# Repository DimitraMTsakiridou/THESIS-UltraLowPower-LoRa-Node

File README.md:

# Custom Ultra-Low Power LoRa Node for Autonomous Telemetry

Aiming to address the challenges of remote water quality monitoring and bypass the complexity of standard LoRaWAN networks, this repository contains the from-scratch design, end-to-end implementation, and extensive experimental evaluation of a custom, energy-autonomous LoRa telemetry node.

<p align="center">
  
  &nbsp; &nbsp;
  
</p>

## 🚀 Key Achievements & Architecture

### 🛠️ Hardware Design
* **Custom PCB:** Designed a 4-layer Printed Circuit Board (PCB) based on the **STM32WL55 System-on-Chip**.
* **Zero Leakage:** Incorporated a PMOS load switch to completely cut off power to the water quality sensors (Atlas Scientific) during sleep periods, eliminating leakage currents.

### 💻 Firmware & Security
* **Protocol:** Developed a lightweight, custom Peer-to-Peer (P2P) communication protocol.
* **Cybersecurity:** Shifted data security to the application layer, utilizing hardware-based **AES-256 encryption** and dynamic frame counters to prevent deliberate replay attacks.

### ⚡ Performance & Energy Efficiency
* **Energy-Neutral Operation:** The custom board records an average consumption of merely **261 μA** per 15-minute duty cycle. This ensures a theoretical battery autonomy of over 400 days. Coupled with a 5W solar panel, the system becomes completely energy-neutral.
* **Long-Range Telemetry:** Established a reliable wireless link over a distance of **11 km** under Line-of-Sight (LoS) conditions, demonstrating outstanding noise immunity (SNR -18 dB).

### 🧪 SDR Validation & Stress Testing
The reliability of the physical layer and the system's cybersecurity were validated in a laboratory environment using Software-Defined Radio (**USRP B210**) equipment. 
* Achieved a **90.4% Packet Delivery Ratio (PDR)** under severe congestion stress tests.
* Successfully prevented deliberate replay and interception attacks.

---
**Keywords:** Water Quality Telemetry, Internet of Things (IoT), LoRa, LPWAN, Custom Hardware (PCB), Energy Harvesting, Cybersecurity, Software-Defined Radio (SDR).

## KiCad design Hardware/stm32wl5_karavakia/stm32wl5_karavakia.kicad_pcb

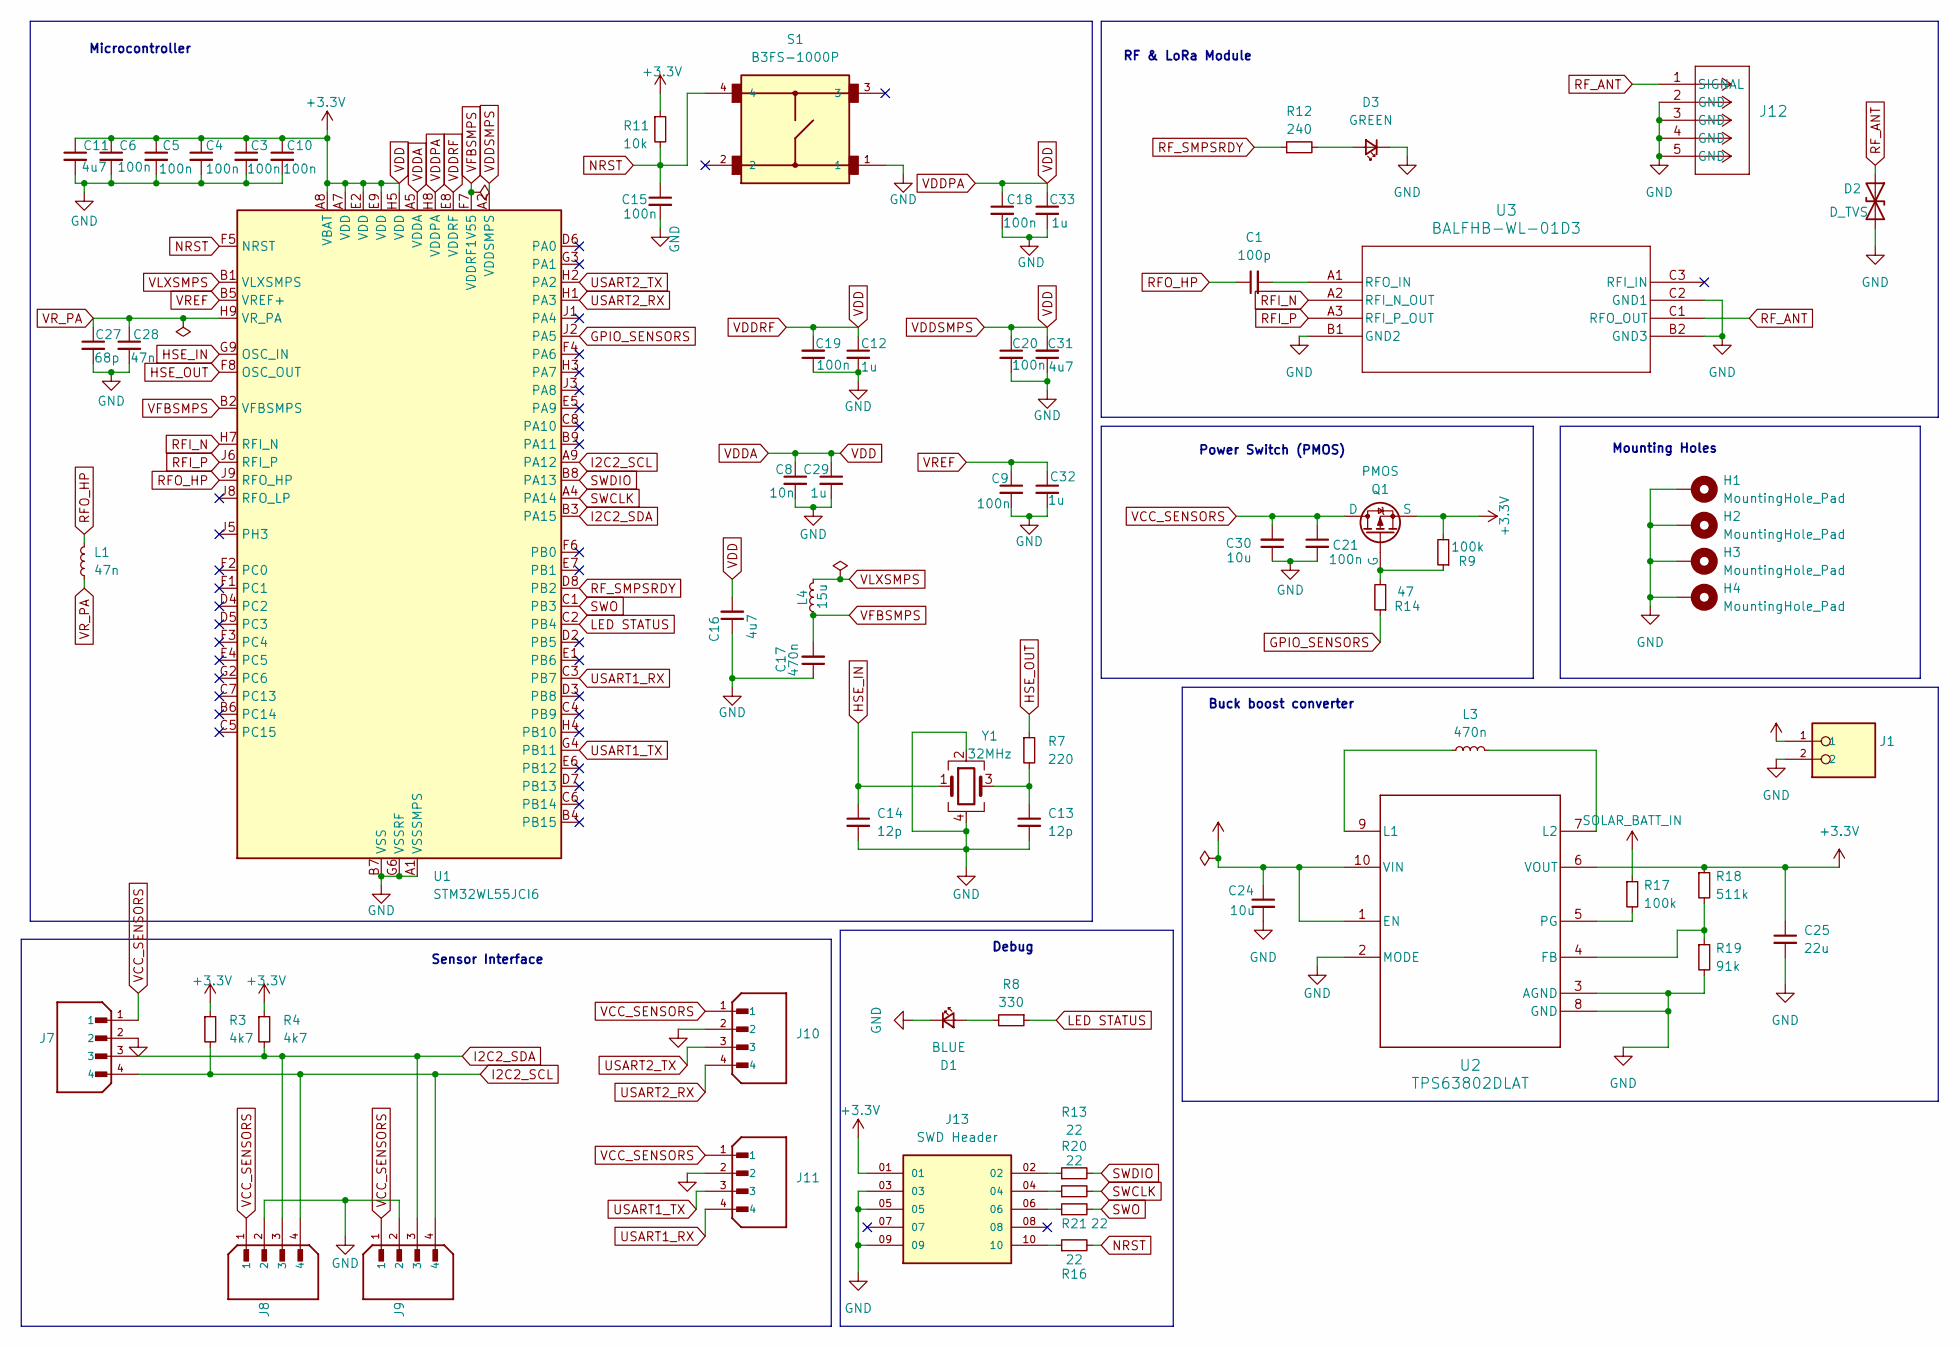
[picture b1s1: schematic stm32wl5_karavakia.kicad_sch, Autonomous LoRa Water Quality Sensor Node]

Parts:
C1: 100p; C_0402_1005Metric
C3, C4, C5, C6, C9, C10, C15, C18, C19, C20, C21: 100n; CAPC1608X90N
C8: 10n; CAPC1608X90N
C11, C16, C31: 4u7; CAPC2012X135N
C12, C29, C32, C33: 1u; CAPC1005X55N
C13, C14: 12p; CAPC1608X90N
C17: 470n; CAPC1608X90N
C24, C30: 10u; CAPC2012X135N
C25: 22u; CAPC2012X140N
C27: 68p; CAPC1005X55N
C28: 47n; CAPC1005X55N
D1: BLUE; LED_XL-2012SURC_XLG
D2: D_TVS; INDC1005X45
D3: GREEN; LED_APT2012_SMD-2P0X1P25_KNB
H1, H2, H3, H4: MountingHole_Pad; MountingHole_3.2mm_M3_Pad_Via
J1: PHOENIX_1935161; PARTREV 14.12.2022
J7, J8, J9, J10, J11: JST_B4B-XH-A; PARTREV 7/4/21
J12: CONN_901-143-6RFX_AMP
J13: SWD Header; SAMTEC_FTSH-105-XX-X-DV; PARTREV H
L1: 47n; LQW15CNR20J00B
L3: 470n; IND_IHLP_1616_BZ_VIS
L4: 15u; INDC2012X145N
Q1: PMOS; SOT-23-3L_AOS
R3, R4: 4k7; R_0805_2012Metric_Pad1.20x1.40mm_HandSolder
R7: 220; R_0805_2012Metric_Pad1.20x1.40mm_HandSolder
R8: 330; R_0805_2012Metric_Pad1.20x1.40mm_HandSolder
R9, R17: 100k; R_0805_2012Metric_Pad1.20x1.40mm_HandSolder
R11: 10k; R_0805_2012Metric_Pad1.20x1.40mm_HandSolder
R12: 240; R_0805_2012Metric_Pad1.20x1.40mm_HandSolder
R13, R16, R20, R21: 22; R_0805_2012Metric_Pad1.20x1.40mm_HandSolder
R14: 47; RES_R0805_ROM
R18: 511k; R_0805_2012Metric_Pad1.20x1.40mm_HandSolder
R19: 91k; R_0805_2012Metric_Pad1.20x1.40mm_HandSolder
S1: B3FS-1000P; SOIC_FS-1000P_OMR
U1: STM32WL55JCI6; UFBGA73_5X5_STM_1
U2: TPS63802DLAT; DLA0010A
U3: BALFHB-WL-01D3; CSPG8_STM
Y1: 32MHz; NX2016SA_NDK

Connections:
GND: C3.2, C4.2, C5.2, C6.2, C8.2, C9.2, C10.2, C11.2, C12.2, C13.2, C14.2, C15.2, C16.1, C17.1, C18.2, C19.1, C20.2, C21.2, C24.2, C25.2, C27.2, C28.2, C29.2, C30.1, C31.1, C32.2, C33.2, D1.1 (K), D2.2 (A2), D3.1 (K), H1.1, H2.1, H3.1, H4.1, J1.2, J7.2, J8.2, J9.2, J10.2, J11.2, J12.2 (GND), J12.3 (GND), J12.4 (GND), J12.5 (GND), J13.03, J13.05, J13.09, R19.2, S1.1, U1.A1 (VSSSMPS), U1.B7 (VSS), U1.D9 (VSS), U1.E3 (VSS), U1.G5 (VSS), U1.G6 (VSSRF), U1.G7 (VSSRF), U1.G8 (VSSRF), U1.H6 (VSSRF), U2.2 (MODE), U2.3 (AGND), U2.8 (GND), U3.B1 (GND2), U3.B2 (GND3), U3.C2 (GND1), Y1.2, Y1.4
GPIO_SENSORS: R14.1, U1.J2 (PA5)
HSE_IN: C14.1, U1.G9 (OSC_IN), Y1.1
HSE_OUT: R7.1, U1.F8 (OSC_OUT)
I2C2_SCL: J7.4, J8.4, J9.4, R3.2, U1.A9 (PA12)
I2C2_SDA: J7.3, J8.3, J9.3, R4.2, U1.B3 (PA15)
LED STATUS: R8.1, U1.C2 (PB4)
NRST: C15.1, R11.2, R16.2, S1.4, U1.F5 (NRST)
unnamed: C13.1, R7.2, Y1.3
unnamed: D1.2 (A), R8.2
unnamed: D3.2 (A), R12.2
unnamed: J13.02, R13.1
unnamed: J13.04, R20.1
unnamed: J13.06, R21.1
unnamed: J13.10, R16.1
unnamed: Q1.2 (G), R9.1, R14.2
unnamed: R18.2, R19.1, U2.4 (FB)
unnamed: L3.1, U2.9 (L1)
unnamed: L3.2, U2.7 (L2)
unnamed: R17.2, U2.5 (PG)
unnamed: C1.2, U3.A1 (RFO_IN)
RFI_N: U1.H7 (RFI_N), U3.A2 (RFI_N_OUT)
RFI_P: U1.J6 (RFI_P), U3.A3 (RFI_P_OUT)
RFO_HP: C1.1, L1.2, U1.J9 (RFO_HP)
RF_ANT: D2.1 (A1), J12.1 (SIGNAL), U3.C1 (RFO_OUT)
RF_SMPSRDY: R12.1, U1.D8 (PB2)
SOLAR_BATT_IN: C24.1, J1.1, R17.1, U2.1 (EN), U2.10 (VIN)
SWCLK: R20.2, U1.A4 (PA14)
SWDIO: R13.2, U1.B8 (PA13)
SWΟ: R21.2, U1.C1 (PB3)
USART1_RX: J11.4, U1.C3 (PB7)
USART1_TX: J11.3, U1.G4 (PB11)
USART2_RX: J10.4, U1.H1 (PA3)
USART2_TX: J10.3, U1.H2 (PA2)
VCC_SENSORS: C21.1, C30.2, J7.1, J8.1, J9.1, J10.1, J11.1, Q1.1 (D)
VDD: C3.1, C4.1, C5.1, C6.1, C8.1, C10.1, C11.1, C12.1, C16.2, C18.1, C19.2, C20.1, C25.1, C29.1, C31.2, C33.1, J13.01, Q1.3 (S), R3.1, R4.1, R9.2, R11.1, R18.1, U1.A2 (VDDSMPS), U1.A5 (VDDA), U1.A7 (VDD), U1.A8 (VBAT), U1.E2 (VDD), U1.E8 (VDDRF), U1.E9 (VDD), U1.H5 (VDD), U1.H8 (VDDPA), U2.6 (VOUT)
VFBSMPS: C17.2, L4.1, U1.B2 (VFBSMPS), U1.F7 (VDDRF1V55)
VLXSMPS: L4.2, U1.B1 (VLXSMPS)
VREF: C9.1, C32.1, U1.B5 (VREF+)
VR_PA: C27.1, C28.1, L1.1, U1.H9 (VR_PA)

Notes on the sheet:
Microcontroller
RF & LoRa Module
Mounting Holes
Debug
Power Switch (PMOS)
Buck boost converter
Sensor Interface

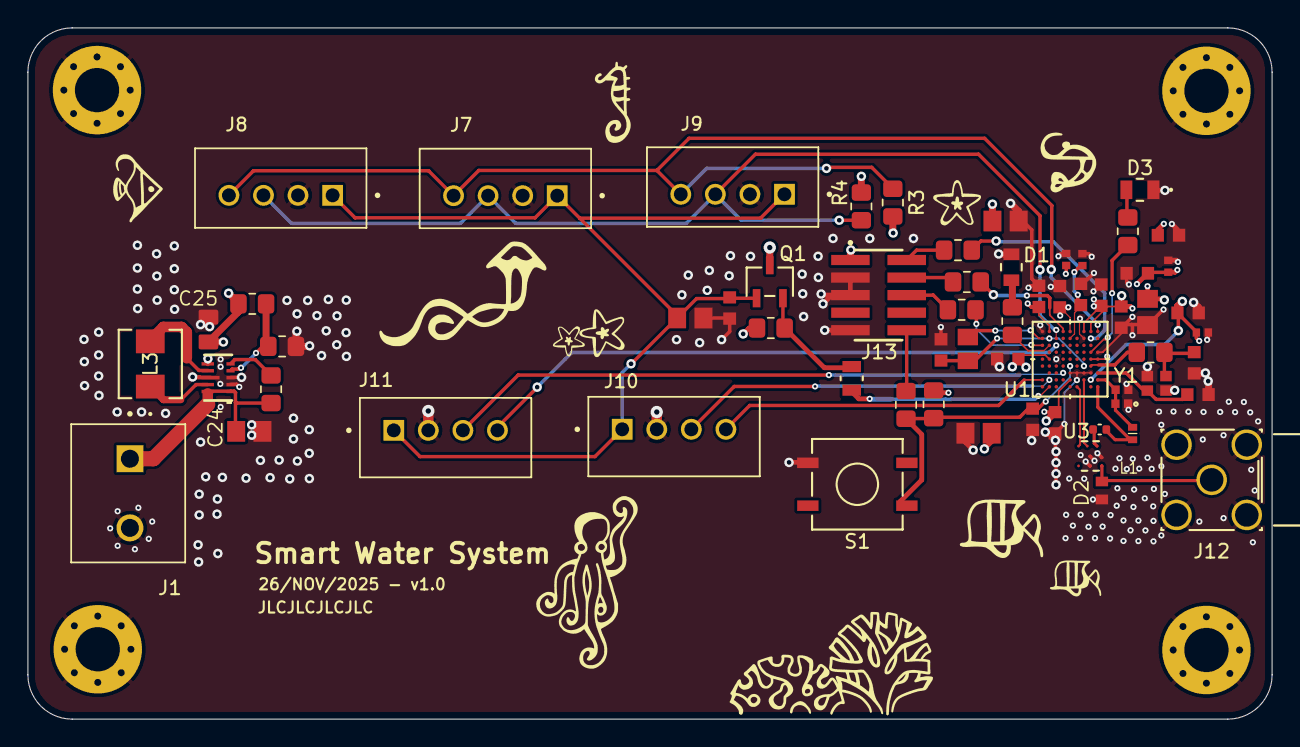
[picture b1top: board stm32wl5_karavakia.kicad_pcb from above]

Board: 4 copper layers, 90.0 x 50.0 mm, 67 parts (0 on the bottom side), 40 nets.

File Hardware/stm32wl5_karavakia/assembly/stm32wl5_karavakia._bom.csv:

"Id";"Designator";"Footprint";"Quantity";"Designation";"Supplier and ref";
1;"C18,C4,C15,C20,C6,C3,C19,C9,C10,C5,C21";"CAPC1608X90N";11;"100n";;;
2;"S1";"SOIC_FS-1000P_OMR";1;"B3F-1000";;;
3;"J12";"COAX4_901-144-8RFX_AMP";1;"~";;;
4;"R21,R20,R13,R16";"R_0805_2012Metric_Pad1.20x1.40mm_HandSolder";4;"22";;;
5;"D3";"LED_APT2012_SMD-2P0X1P25_KNB";1;"GREEN";;;
6;"J8,J7,J10,J9,J11";"JST_B4B-XH-A";5;"~";;;
7;"C8";"CAPC1608X90N";1;"10n";;;
8;"R3,R4";"R_0805_2012Metric_Pad1.20x1.40mm_HandSolder";2;"4k7";;;
9;"U2";"DLA0010A";1;"TPS63802DLAT";;;
10;"D1";"LED_XL-2012SURC_XLG";1;"BLUE";;;
11;"R18";"R_0805_2012Metric_Pad1.20x1.40mm_HandSolder";1;"511k";;;
12;"C11,C31,C16";"CAPC2012X135N";3;"4u7";;;
13;"R12";"R_0805_2012Metric_Pad1.20x1.40mm_HandSolder";1;"240";;;
14;"J13";"SAMTEC_FTSH-105-XX-X-DV";1;"SWD Header";;;
15;"C30,C24";"CAPC2012X135N";2;"10u";;;
16;"R7";"R_0805_2012Metric_Pad1.20x1.40mm_HandSolder";1;"220";;;
17;"U3";"CSPG8_STM";1;"BALFHB-WL-01D3";;;
18;"Q1";"SOT-23-3L_AOS";1;"PMOS";;;
19;"R14";"RES_R0805_ROM";1;"47";;;
20;"C25";"CAPC2012X140N";1;"22u";;;
21;"C17";"CAPC1608X90N";1;"470n";;;
22;"C12,C32,C33,C29";"CAPC1005X55N";4;"1u";;;
23;"C1";"C_0402_1005Metric";1;"100p";;;
24;"C28";"CAPC1005X55N";1;"47n";;;
25;"C27";"CAPC1005X55N";1;"68p";;;
26;"R9,R17";"R_0805_2012Metric_Pad1.20x1.40mm_HandSolder";2;"100k";;;
27;"Y1";"NX2016SA_NDK";1;"32MHz";;;
28;"L1";"LQW15CNR20J00B";1;"47n";;;
29;"J1";"PHOENIX_1935161";1;"~";;;
30;"R8";"R_0805_2012Metric_Pad1.20x1.40mm_HandSolder";1;"330";;;
31;"R11";"R_0805_2012Metric_Pad1.20x1.40mm_HandSolder";1;"10k";;;
32;"L3";"IND_IHLP_1616_BZ_VIS";1;"470n";;;
33;"L4";"INDC2012X145N";1;"15u";;;
34;"C14,C13";"CAPC1608X90N";2;"12p";;;
35;"R19";"R_0805_2012Metric_Pad1.20x1.40mm_HandSolder";1;"91k";;;
36;"D2";"INDC1005X45";1;"D_TVS";;;
37;"U1";"UFBGA73_5X5_STM_1";1;"STM32WL55JCI6";;;

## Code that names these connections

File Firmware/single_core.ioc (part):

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Mcu.Name=STM32WLE5JCIx
Mcu.Package=UFBGA73
Mcu.UserName=STM32WLE5JCIx
PA11.GPIOParameters=GPIO_Pu
PA11.GPIO_Pu=GPIO_NOPULL
PA11.Signal=I2C2_SDA
PA13.Mode=Serial_Wire
PA13.Signal=DEBUG_JTMS-SWDIO
PA14.Mode=Serial_Wire
PA14.Signal=DEBUG_JTCK-SWCLK
PA2.Mode=Asynchronous
PA2.Signal=USART2_TX
PA3.Mode=Asynchronous
PA3.Signal=USART2_RX
PA5.Signal=GPIO_Output
PB2.Mode=RF-SMPSRDY
PB2.Signal=DEBUG_RF-SMPSRDY
PB3.Signal=DEBUG_JTDO-SWO
PB4.GPIOParameters=PinState,GPIO_Label
PB4.GPIO_Label=LED_STATUS
PB4.PinState=GPIO_PIN_SET
PB4.Signal=GPIO_Output
RCC.HSE_VALUE=32000000
RCC.SYSCLKFreq_VALUE=48000000
RCC.SYSCLKSource=RCC_SYSCLKSOURCE_PLLCLK
board=custom

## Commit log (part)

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2026-06-08 Initial commit for Thesis
2026-06-08 Added README with project overview, organized images, and removed stray files
2026-06-08 Organized images into Images folder and updated README links
2026-06-08 Updated README links
2026-06-08 Added Images folder and fixed README links
2026-06-08 Upload image files for README
